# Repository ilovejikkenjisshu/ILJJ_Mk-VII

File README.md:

View this project on [CADLAB.io](https://cadlab.io/project/2309). 

# ILJJ_Mk-VII

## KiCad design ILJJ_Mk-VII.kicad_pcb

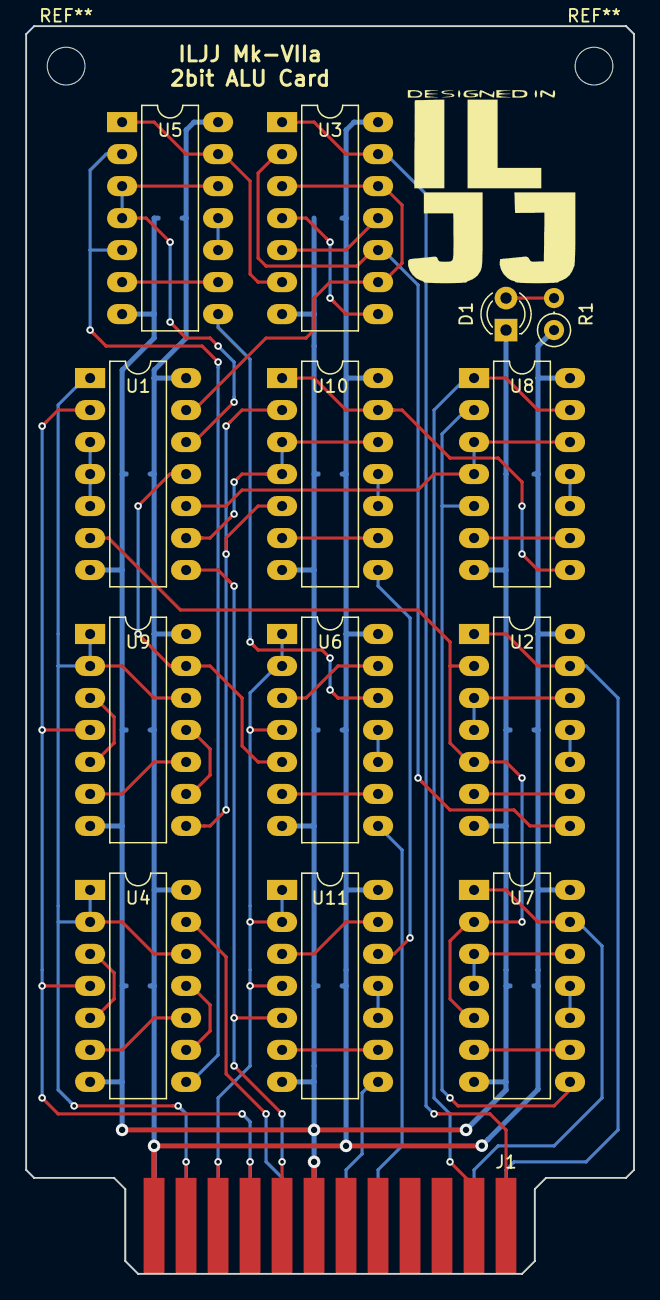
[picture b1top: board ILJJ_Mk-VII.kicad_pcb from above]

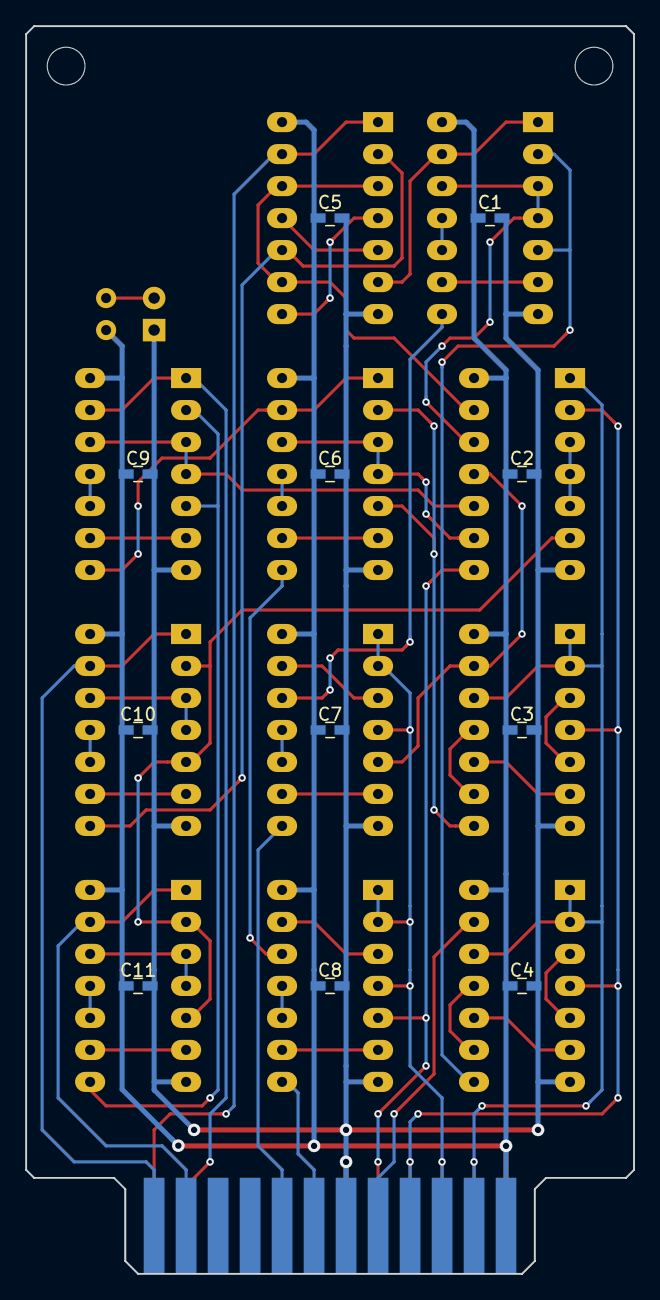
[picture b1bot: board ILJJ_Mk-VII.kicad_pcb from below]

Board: 2 copper layers, 48.3 x 99.1 mm, 25 parts (11 on the bottom side), 55 nets.

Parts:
C1, C2, C3, C4, C5, C6, C7, C8, C9, C10, C11: 0.1µF; C_0603_HandSoldering
D1: POWER; LED_D3.0mm
J1: Conn_02x12; 5530843-1_edge
R1: R; R_Axial_DIN0207_L6.3mm_D2.5mm_P2.54mm_Vertical
U1, U2, U3, U4, U5, U6, U7, U8, U9, U10, U11: 74LS00; DIP-14_W7.62mm_LongPads

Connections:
/A0: J1.23, U3.1, U3.13
/A1: J1.21, U8.1, U8.13
/B0: J1.24, U2.1, U2.13
/B1: J1.22, U7.1, U7.13
/Cin: J1.10, U4.13
/Cout: J1.9, U1.8, U11.5
/F0: J1.7, J1.8, U1.2, U4.4, U9.4
/F1: J1.5, J1.6, U6.1, U6.2, U6.4, U11.1, U11.2, U11.4
/F2: J1.3, J1.4, U1.1, U4.1, U4.2, U4.12, U9.1, U9.2, U9.12
/FA0_B: U2.8, U3.2, U3.10
/FA0_Cin: U4.8, U5.2, U5.5
/FA0_S: U5.8, U6.12
/FA1_B: U7.8, U8.2, U8.5
/FA1_Cin: U9.8, U10.2, U10.5
/FA1_S: U10.8, U11.12
/IBC: U1.11, U6.5, U9.13
/S0: J1.16, U6.8
/S1: J1.14, U11.8
/SUB_FLAG: U1.6, U2.2, U2.5, U7.2, U7.5
GND: C1.2, C2.2, C3.2, C4.2, C5.2, C6.2, C7.2, C8.2, C9.2, C10.2, C11.2, D1.1, J1.11, J1.12, U1.7, U2.7, U3.7, U4.7, U5.7, U6.7, U7.7, U8.7, U9.7, U10.7, U11.7
unnamed: D1.2, R1.2
unnamed: U1.3, U1.4, U1.5
unnamed: U1.9, U10.3, U10.4, U10.12
unnamed: U1.10, U8.3, U8.4, U8.12
unnamed: U1.12, U5.3, U5.4, U5.12
unnamed: U1.13, U3.3, U3.9, U3.12
unnamed: U2.6, U2.9
unnamed: U2.10, U2.11
unnamed: U2.3, U2.4, U2.12
unnamed: U3.4, U3.8
unnamed: U3.6, U5.1, U5.13
unnamed: U3.5, U3.11
unnamed: U4.3, U4.5
unnamed: U4.6, U4.10
unnamed: U4.9, U4.11
unnamed: U5.6, U5.9
unnamed: U5.10, U5.11
unnamed: U6.6, U6.9
unnamed: U6.10, U6.11
unnamed: U6.3, U6.13
unnamed: U7.6, U7.9
unnamed: U7.10, U7.11
unnamed: U7.3, U7.4, U7.12
unnamed: U8.6, U8.9
unnamed: U8.10, U8.11
unnamed: U9.3, U9.5
unnamed: U9.6, U9.10
unnamed: U9.9, U9.11
unnamed: U8.8, U10.1, U10.13
unnamed: U10.6, U10.9
unnamed: U10.10, U10.11
unnamed: U11.6, U11.9
unnamed: U11.10, U11.11
unnamed: U11.3, U11.13
VCC: C1.1, C2.1, C3.1, C4.1, C5.1, C6.1, C7.1, C8.1, C9.1, C10.1, C11.1, J1.1, J1.2, R1.1, U1.14, U2.14, U3.14, U4.14, U5.14, U6.14, U7.14, U8.14, U9.14, U10.14, U11.14

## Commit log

2018-11-20 [clean] 配線を微調整
2018-11-20 [add] ネジ穴
2018-11-20 [update] 外形の面取り
2018-11-20 [clean] 配線の微調整
2018-11-22 [fix] コネクタの両側短絡すべきポートが短絡していないのを修正
    この方法で合ってるのか不安
2018-11-22 [add] some logos
2019-03-05 [fix] ICの干渉を解消 / ILJJのロゴを小さく
    かなりレイアウトが変わった
2019-03-05 [change] CinとCoutを交換
2019-03-05 [change] パワーランプの位置を変更
2019-03-05 [add] board info
2019-11-23 Backlink to CADLAB.io has been added.
